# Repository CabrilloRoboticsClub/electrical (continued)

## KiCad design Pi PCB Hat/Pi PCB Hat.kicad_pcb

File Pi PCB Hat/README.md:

# Pi PCB Hat

https://github.com/CabrilloRoboticsClub/electrical/wiki/Pi-Hat-PCB

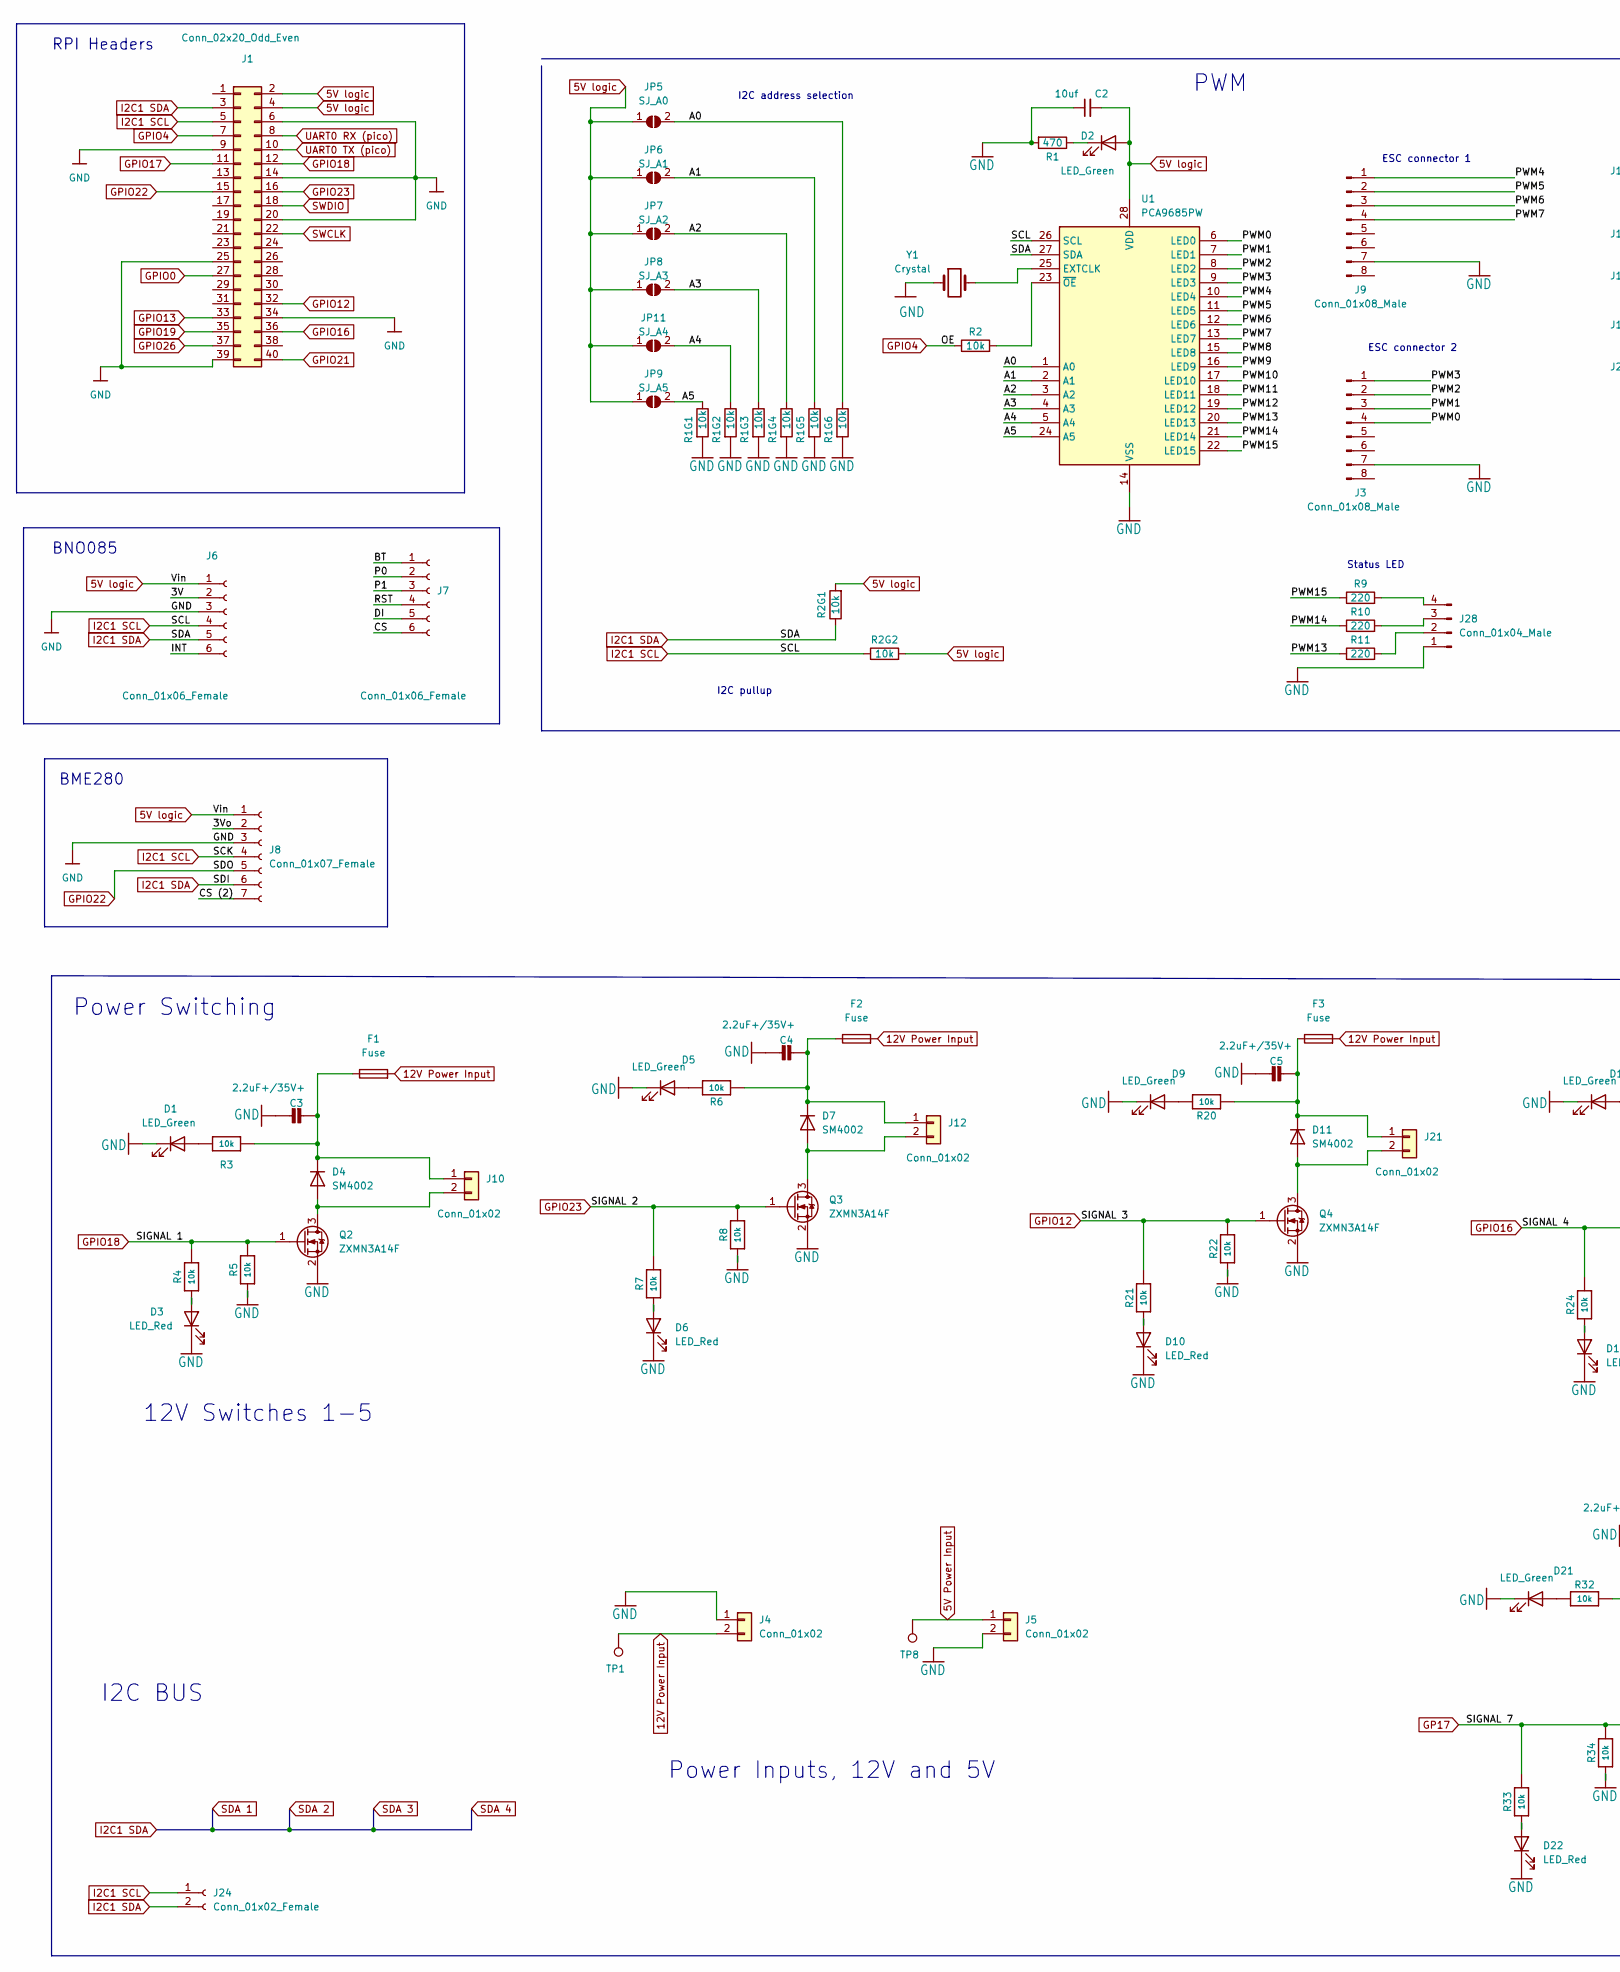
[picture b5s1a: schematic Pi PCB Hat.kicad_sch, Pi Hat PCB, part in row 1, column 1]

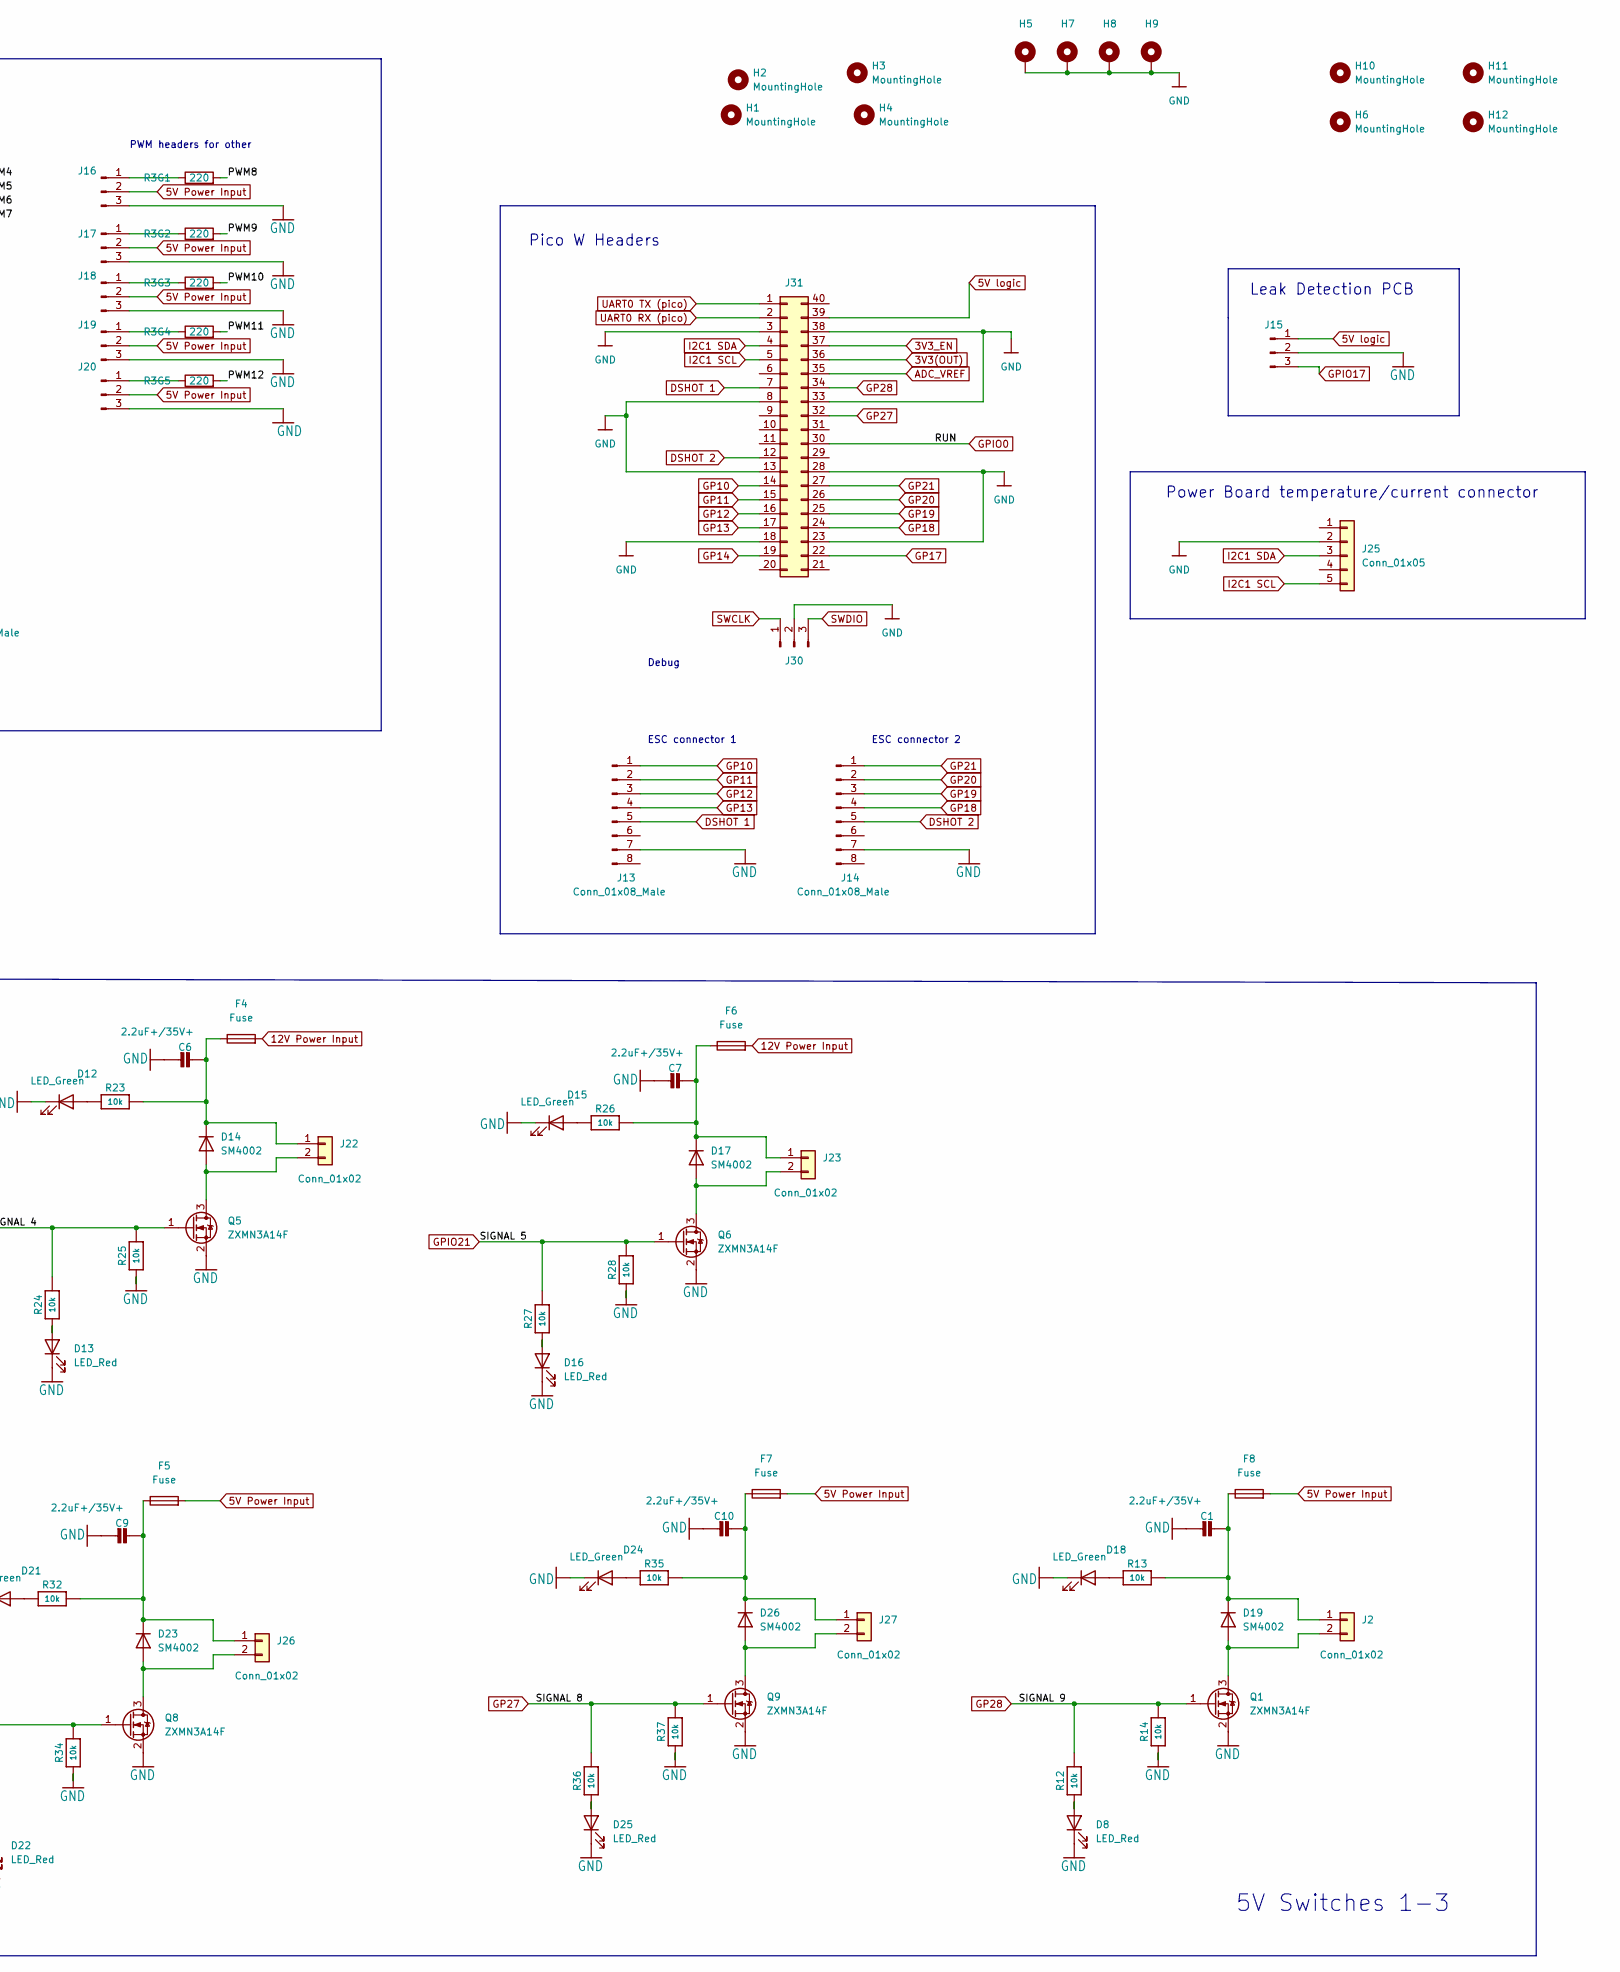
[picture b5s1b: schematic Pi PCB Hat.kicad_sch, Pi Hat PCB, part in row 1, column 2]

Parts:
C1, C3, C4, C5, C6, C7, C9, C10: 2.2uF+/35V+; C_0805_2012Metric
C2: 10uf; C_0805_2012Metric
D1, D2, D5, D9, D12, D15, D18, D21, D24: LED_Green; LED_0603_1608Metric
D3, D6, D8, D10, D13, D16, D22, D25: LED_Red; LED_0603_1608Metric
D4, D7, D11, D14, D17, D19, D23, D26: SM4002; D_SOD-123F
F1, F2, F3, F4, F5, F6, F7, F8: Fuse; Fuse_0805_2012Metric
H1, H2, H3, H4: MountingHole; MountingHole_3.2mm_M3_DIN965_Pad
H5, H7, H8, H9: MountingHole_Pad; MountingHole_2.7mm_M2.5_DIN965_Pad
H6, H10, H11, H12: MountingHole; MountingHole_2.2mm_M2_DIN965_Pad
J1: Conn_02x20_Odd_Even; PinSocket_2x20_P2.54mm_Vertical
J2, J10, J12, J21, J22, J23, J26, J27: Conn_01x02; Molex_Micro-Latch_53253-0270_1x02_P2.00mm_Vertical_3D_model
J3, J9, J13, J14: Conn_01x08_Male; JST_SH_BM08B-SRSS-TB_1x08-1MP_P1.00mm_Vertical_3D
J4: Conn_01x02; AMASS_XT30PW-F_1x02_P2.50mm_Horizontal
J5: Conn_01x02; Molex_KK-396_A-41791-0002_1x02_P3.96mm_Vertical
J6, J7: Conn_01x06_Female; PinSocket_1x06_P2.54mm_Vertical
J8: Conn_01x07_Female; PinSocket_1x07_P2.54mm_Vertical
J15, J16, J17, J18, J19, J20: Conn_01x03_Male; PinHeader_1x03_P2.54mm_Vertical
J24: Conn_01x02_Female; PinHeader_1x02_P2.54mm_Vertical
J25: Conn_01x05; Molex_PicoBlade_53047-0510_1x05_P1.25mm_Vertical
J28: Conn_01x04_Male; Molex_PicoBlade_53047-0410_1x04_P1.25mm_Vertical
J30: Conn_01x03_Pin; PinSocket_1x03_P2.54mm_Vertical
J31: Conn_02x20_Counter_Clockwise; PinSocket_1x20_P2.54mm_Vertical
JP5: SJ_A0; SolderJumper-2_P1.3mm_Open_RoundedPad1.0x1.5mm
JP6: SJ_A1; SolderJumper-2_P1.3mm_Open_RoundedPad1.0x1.5mm
JP7: SJ_A2; SolderJumper-2_P1.3mm_Open_RoundedPad1.0x1.5mm
JP8: SJ_A3; SolderJumper-2_P1.3mm_Open_RoundedPad1.0x1.5mm
JP9: SJ_A5; SolderJumper-2_P1.3mm_Open_RoundedPad1.0x1.5mm
JP11: SJ_A4; SolderJumper-2_P1.3mm_Open_RoundedPad1.0x1.5mm
Q1, Q2, Q3, Q4, Q5, Q6, Q8, Q9: ZXMN3A14F; SOT-23
R1: 470; R_0805_2012Metric
R1G1, R1G2, R1G3, R1G4, R1G5, R1G6, R2, R2G1, R2G2, R3, R4, R5, R6, R7, R8, R12, R13, R14, R20, R21, R22, R23, R24, R25, R26, R27, R28, R32, R33, R34, R35, R36, R37: 10k; R_0805_2012Metric
R3G1, R3G2, R3G3, R3G4, R3G5, R9, R10, R11: 220; R_0805_2012Metric
TP1, TP8: TestPoint; TestPoint_Pad_1.5x1.5mm
U1: PCA9685PW; TSSOP-28_4.4x9.7mm_P0.65mm
Y1: Crystal; Crystal_HC49-U_Vertical

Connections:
3V3(OUT): J31.36
3V3_EN: J31.37
5V Power Input: F5.2, F7.2, F8.2, J5.1, J16.2, J17.2, J18.2, J19.2, J20.2, TP8.1
5V logic: C2.2, D2.2 (A), J1.2, J1.4, J6.1, J8.1, J15.1, J31.39, JP5.1 (A), JP6.1 (A), JP7.1 (A), JP8.1 (A), JP9.1 (A), JP11.1 (A), R2G1.2, R2G2.2, U1.28 (VDD)
12V Power Input: F1.2, F2.2, F3.2, F4.2, F6.2, J4.2, TP1.1; also elsewhere on the board
/3V: J6.2
/3Vo: J8.2
/A0: JP5.2 (B), R1G6.1, U1.1 (A0)
/A1: JP6.2 (B), R1G5.1, U1.2 (A1)
/A2: JP7.2 (B), R1G4.1, U1.3 (A2)
/A3: JP8.2 (B), R1G3.1, U1.4 (A3)
/A4: JP11.2 (B), R1G2.1, U1.5 (A4)
/A5: JP9.2 (B), R1G1.1, U1.24 (A5)
/BT: J7.1
/CS: J7.6
/CS (2): J8.7
/DI: J7.5
/INT: J6.6
/P0: J7.2
/P1: J7.3
/PWM0: J3.4, U1.6 (LED0)
/PWM1: J3.3, U1.7 (LED1)
/PWM2: J3.2, U1.8 (LED2)
/PWM3: J3.1, U1.9 (LED3)
/PWM4: J9.1, U1.10 (LED4)
/PWM5: J9.2, U1.11 (LED5)
/PWM6: J9.3, U1.12 (LED6)
/PWM7: J9.4, U1.13 (LED7)
/PWM8: R3G1.2, U1.15 (LED8)
/PWM9: R3G2.2, U1.16 (LED9)
/PWM10: R3G3.2, U1.17 (LED10)
/PWM11: R3G4.2, U1.18 (LED11)
/PWM12: R3G5.2, U1.19 (LED12)
/PWM13: R11.1, U1.20 (LED13)
/PWM14: R10.1, U1.21 (LED14)
/PWM15: R9.1, U1.22 (LED15)
/RST: J7.4
ADC_VREF: J31.35
DSHOT 1: J13.5, J31.7
DSHOT 2: J14.5, J31.12
GND: C1.2, C2.1, C3.2, C4.2, C5.2, C6.2, C7.2, C9.2, C10.2, D1.1 (K), D3.1 (K), D5.1 (K), D6.1 (K), D8.1 (K), D9.1 (K), D10.1 (K), D12.1 (K), D13.1 (K), D15.1 (K), D16.1 (K), D18.1 (K), D21.1 (K), D22.1 (K), D24.1 (K), D25.1 (K), H5.1, H7.1, H8.1, H9.1, J1.6, J1.9, J1.14, J1.20, J1.25, J1.34, J1.39, J3.7, J4.1, J5.2, J6.3, J8.3, J9.7, J13.7, J14.7, J15.2, J16.3, J17.3, J18.3, J19.3, J20.3, J25.2, J28.1, J30.2, J31.3, J31.8, J31.13, J31.18, J31.23, J31.28, J31.33, J31.38, Q1.2 (S), Q2.2 (S), Q3.2 (S), Q4.2 (S), Q5.2 (S), Q6.2 (S), Q8.2 (S), Q9.2 (S), R1.2, R1G1.2, R1G2.2, R1G3.2, R1G4.2, R1G5.2, R1G6.2, R5.1, R8.1, R14.1, R22.1, R25.1, R28.1, R34.1, R37.1, U1.14 (VSS), Y1.1; also elsewhere on the board
GP10: J13.1, J31.14
GP11: J13.2, J31.15
GP12: J13.3, J31.16
GP13: J13.4, J31.17
GP14: J31.19
GP17: J31.22, Q8.1 (G), R33.2, R34.2
GP18: J14.4, J31.24
GP19: J14.3, J31.25
GP20: J14.2, J31.26
GP21: J14.1, J31.27
GP27: J31.32, Q9.1 (G), R36.2, R37.2
GP28: J31.34, Q1.1 (G), R12.2, R14.2
GPIO0: J1.27, J31.30
GPIO4: J1.7, R2.1
GPIO12: J1.32, Q4.1 (G), R21.2, R22.2; also elsewhere on the board
GPIO13: J1.33
GPIO16: J1.36, Q5.1 (G), R24.2, R25.2; also elsewhere on the board
GPIO17: J1.11, J15.3
GPIO18: J1.12, Q2.1 (G), R4.2, R5.2
GPIO19: J1.35
GPIO21: J1.40, Q6.1 (G), R27.2, R28.2; also elsewhere on the board
GPIO22: J1.15, J8.5
GPIO23: J1.16, Q3.1 (G), R7.2, R8.2; also elsewhere on the board
GPIO26: J1.37
I2C1 SCL: J1.5, J6.4, J8.4, J24.1, J25.5, J31.5, R2G2.1, U1.26 (SCL)
I2C1 SDA: J1.3, J6.5, J8.6, J24.2, J25.3, J31.4, R2G1.1, U1.27 (SDA)
unnamed: D1.2 (A), R3.1
unnamed: D2.1 (K), R1.1
unnamed: D3.2 (A), R4.1
unnamed: D4.2 (A), J10.2, Q2.3 (D)
unnamed: C3.1, D4.1 (K), F1.1, J10.1, R3.2
unnamed 72: D5.2 (A), R6.1; also elsewhere on the board
unnamed 73: D6.2 (A), R7.1; also elsewhere on the board
unnamed 74: D7.2 (A), J12.2, Q3.3 (D); also elsewhere on the board
unnamed 75: C4.1, D7.1 (K), F2.1, J12.1, R6.2; also elsewhere on the board
unnamed: D8.2 (A), R12.1
unnamed: D9.2 (A), R20.1
unnamed 78: D10.2 (A), R21.1; also elsewhere on the board
unnamed: D11.2 (A), J21.2, Q4.3 (D)
unnamed 80: C5.1, D11.1 (K), F3.1, J21.1, R20.2; also elsewhere on the board
unnamed: D12.2 (A), R23.1
unnamed 82: D13.2 (A), R24.1; also elsewhere on the board
unnamed: D14.2 (A), J22.2, Q5.3 (D)
unnamed 84: C6.1, D14.1 (K), F4.1, J22.1, R23.2; also elsewhere on the board
unnamed: D15.2 (A), R26.1
unnamed 86: D16.2 (A), R27.1; also elsewhere on the board
unnamed: D17.2 (A), J23.2, Q6.3 (D)
unnamed 88: C7.1, D17.1 (K), F6.1, J23.1, R26.2; also elsewhere on the board
unnamed: D18.2 (A), R13.1
unnamed: D19.2 (A), J2.2, Q1.3 (D)
unnamed: C1.1, D19.1 (K), F8.1, J2.1, R13.2
unnamed: D21.2 (A), R32.1
unnamed: D22.2 (A), R33.1
unnamed: D23.2 (A), J26.2, Q8.3 (D)
unnamed: C9.1, D23.1 (K), F5.1, J26.1, R32.2
unnamed: D24.2 (A), R35.1
unnamed: D25.2 (A), R36.1
unnamed: D26.2 (A), J27.2, Q9.3 (D)
unnamed: C10.1, D26.1 (K), F7.1, J27.1, R35.2
unnamed: J16.1, R3G1.1
unnamed: J17.1, R3G2.1
unnamed: J18.1, R3G3.1
unnamed: J19.1, R3G4.1
unnamed: J20.1, R3G5.1
unnamed: J28.2, R11.2
unnamed: J28.3, R10.2
unnamed: J28.4, R9.2
unnamed: U1.25 (EXTCLK), Y1.2
unnamed: R2.2, U1.23 (~OE)
SWCLK: J1.22, J30.1
SWDIO: J1.18, J30.3
UART0 RX (pico): J1.8, J31.2
UART0 TX (pico): J1.10, J31.1

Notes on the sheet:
Power Switching
I2C BUS
I2C pullup
Debug
ESC connector 2
Status LED
5V Switches 1-3
12V Switches 1-5
Leak Detection PCB
I2C address selection
ESC connector 1
RPI Headers
PWM
BME280
Pico W Headers
Power Inputs, 12V and 5V
PWM headers for other
Power Board temperature/current connector
BNO085

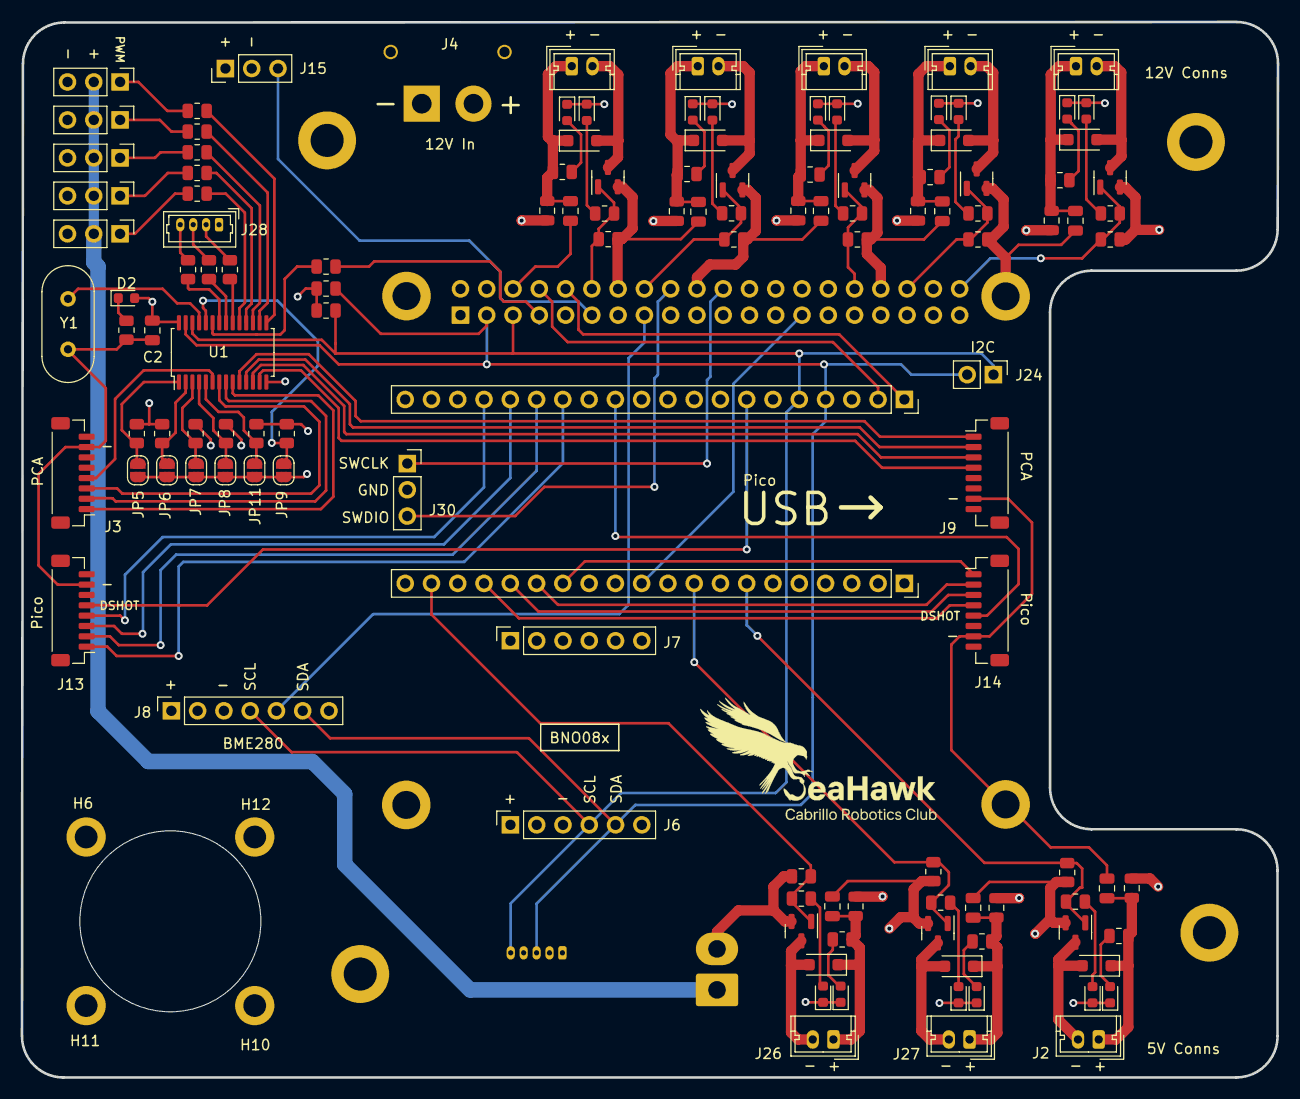
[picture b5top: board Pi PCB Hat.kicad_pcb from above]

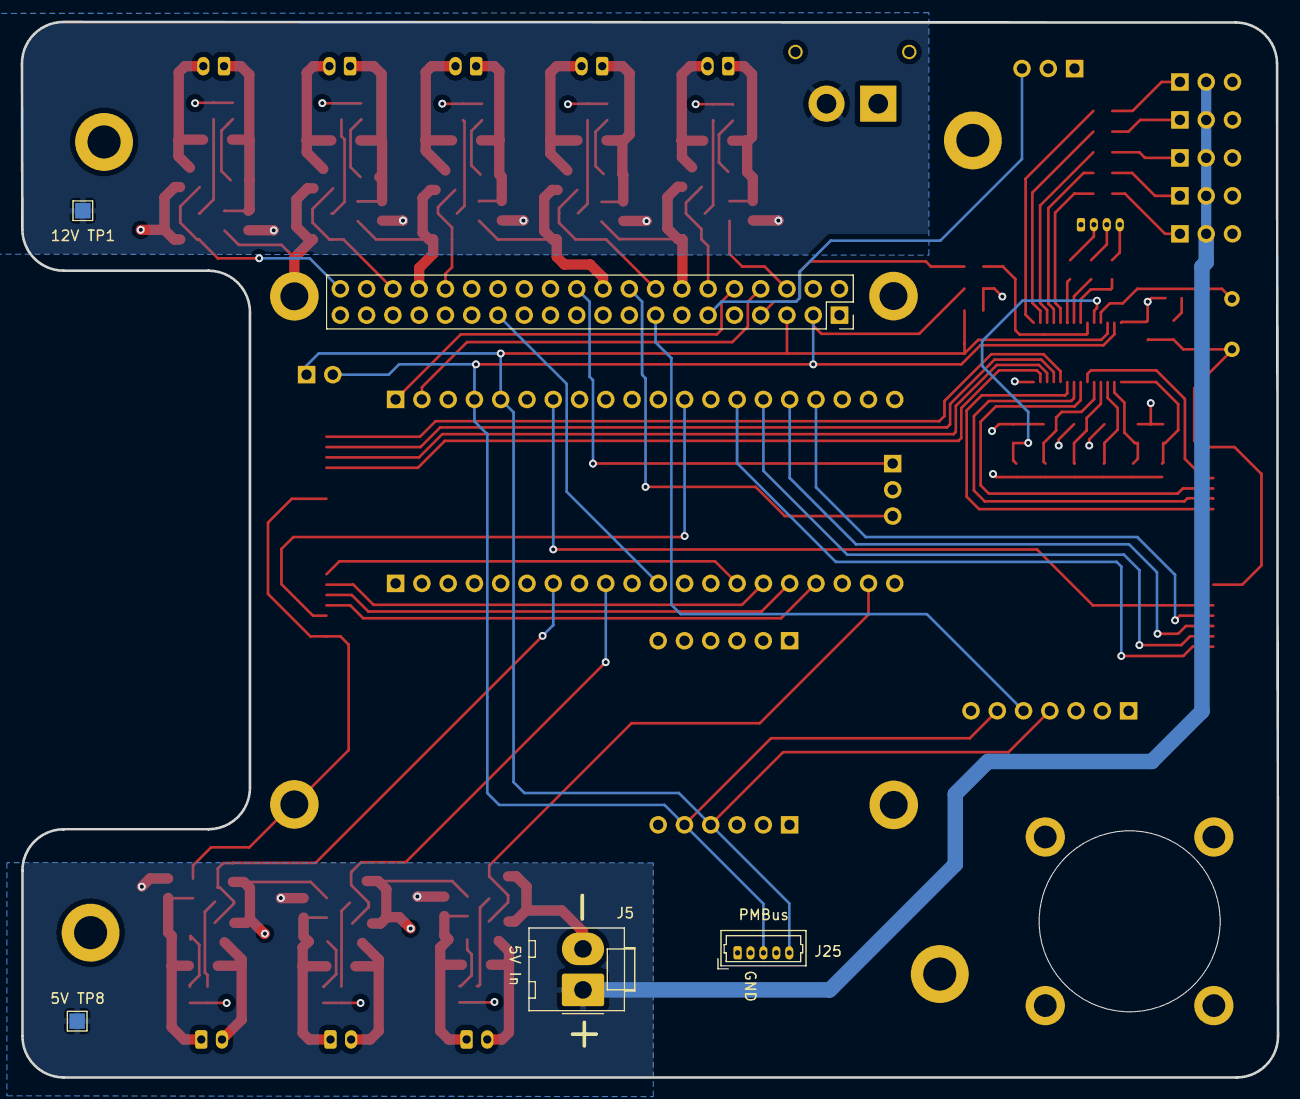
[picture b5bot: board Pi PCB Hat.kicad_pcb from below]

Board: 4 copper layers, 121.4 x 102.0 mm, 143 parts (5 on the bottom side), 97 nets.

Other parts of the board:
locked: 2.2uF+/35V+; C_0805_2012Metric
locked#2, locked#3, locked#4, locked#7, locked#12: 10k; R_0805_2012Metric
locked#5, locked#9, locked#10: Fuse; Fuse_0805_2012Metric
locked#6: ZXMN3A14F; SOT-23
locked#8, locked#11: 2.2uF+/35V+; C_0805_2012Metric

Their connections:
12V Power Input: locked#5.2, locked#9.2, locked#10.2; also elsewhere on the board
GND: locked.2, locked#6.2 (S), locked#8.2, locked#11.2; also elsewhere on the board
GPIO12: locked#2.2; also elsewhere on the board
GPIO16: locked#12.2; also elsewhere on the board
GPIO21: locked#7.2; also elsewhere on the board
GPIO23: locked#3.2, locked#6.1 (G); also elsewhere on the board
unnamed 72: locked#4.1; also elsewhere on the board
unnamed 73: locked#3.1; also elsewhere on the board
unnamed 74: locked#6.3 (D); also elsewhere on the board
unnamed 75: locked#4.2; also elsewhere on the board
unnamed 78: locked#2.1; also elsewhere on the board
unnamed 80: locked.1, locked#5.1; also elsewhere on the board
unnamed 82: locked#12.1; also elsewhere on the board
unnamed 84: locked#9.1, locked#11.1; also elsewhere on the board
unnamed 86: locked#7.1; also elsewhere on the board
unnamed 88: locked#8.1, locked#10.1; also elsewhere on the board

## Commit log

2024-06-30 Create README.md
    add readme
2024-06-30 Update README.md
    added photo
2024-06-30 Update README.md
    added another nice photo and intor
2024-06-30 Update README.md
    photo did not work right before
2024-06-30 Update README.md
    done i think
2024-07-04 pi hat pcb
2024-07-04 Create README.md
    for linking to documention
2024-07-04 added power distrubtion board
2024-07-04 Create README.md
    place for link to documention
2024-07-04 added esc carrier board and added detail to power board BOM
2024-07-04 Create README.md
    place for doc link to go
2024-07-04 add leak sensor board(s)
2024-07-04 Create LICENSE
2024-07-04 adding folder to put relivent photos into
2024-07-04 Update README.md
    added link to wiki
2024-07-06 Add schematic PDF and update KiCad schematic for Power Distribution Board
2024-07-06 added image
2024-07-13 #this is it
2024-08-21 added archived componet libareys
